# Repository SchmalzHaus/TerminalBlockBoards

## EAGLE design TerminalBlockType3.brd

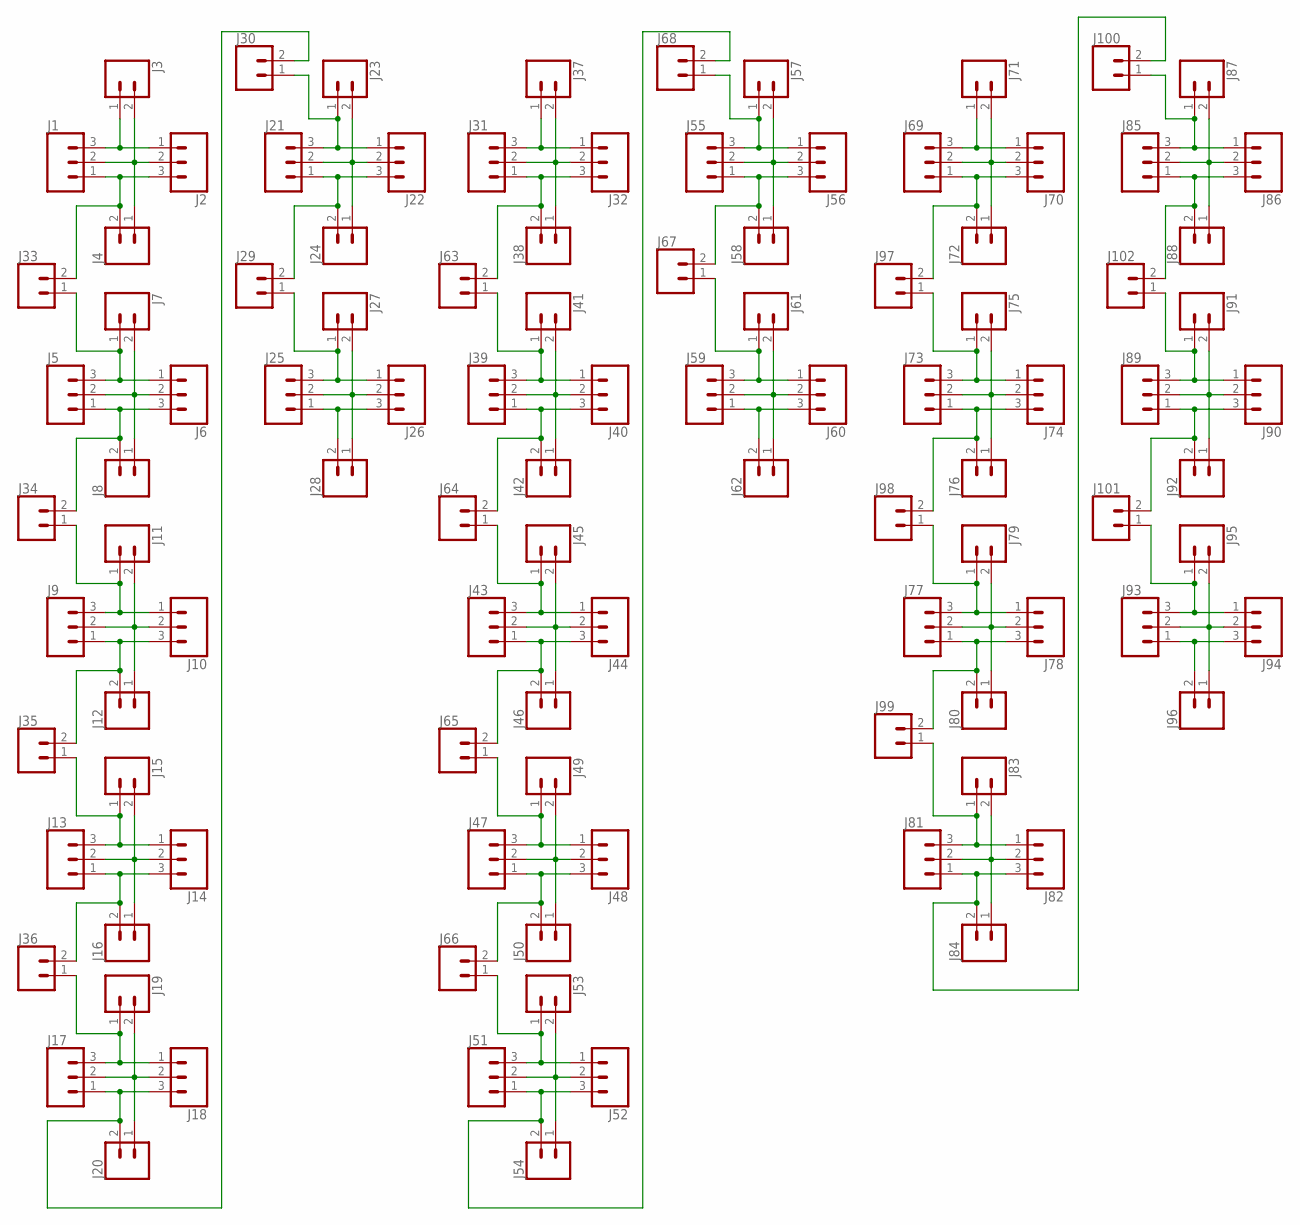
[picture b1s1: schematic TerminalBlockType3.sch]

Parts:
J1, J2, J5, J6, J9, J10, J13, J14, J17, J18, J21, J22, J25, J26, J31, J32, J39, J40, J43, J44, J47, J48, J51, J52, J55, J56, J59, J60, J69, J70, J73, J74, J77, J78, J81, J82, J85, J86, J89, J90, J93, J94: CONN_03SCREW_LOCK; SCREWTERMINAL-3.5MM-3_LOCK.007S
J3, J4, J7, J8, J11, J12, J15, J16, J19, J20, J23, J24, J27, J28, J29, J30, J33, J34, J35, J36, J37, J38, J41, J42, J45, J46, J49, J50, J53, J54, J57, J58, J61, J62, J63, J64, J65, J66, J67, J68, J71, J72, J75, J76, J79, J80, J83, J84, J87, J88, J91, J92, J95, J96, J97, J98, J99, J100, J101, J102: CONN_02; 1X02

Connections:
unnamed: J1.3, J2.1, J3.1
unnamed: J1.2, J2.2, J3.2, J4.1
unnamed: J1.1, J2.3, J4.2, J33.2
unnamed: J5.3, J6.1, J7.1, J33.1
unnamed: J5.2, J6.2, J7.2, J8.1
unnamed: J5.1, J6.3, J8.2, J34.2
unnamed: J9.3, J10.1, J11.1, J34.1
unnamed: J9.2, J10.2, J11.2, J12.1
unnamed: J9.1, J10.3, J12.2, J35.2
unnamed: J13.3, J14.1, J15.1, J35.1
unnamed: J13.2, J14.2, J15.2, J16.1
unnamed: J13.1, J14.3, J16.2, J36.2
unnamed: J17.3, J18.1, J19.1, J36.1
unnamed: J17.2, J18.2, J19.2, J20.1
unnamed: J17.1, J18.3, J20.2, J30.2
unnamed: J21.3, J22.1, J23.1, J30.1
unnamed: J21.2, J22.2, J23.2, J24.1
unnamed: J21.1, J22.3, J24.2, J29.2
unnamed: J25.3, J26.1, J27.1, J29.1
unnamed: J25.2, J26.2, J27.2, J28.1
unnamed: J25.1, J26.3, J28.2
unnamed: J31.3, J32.1, J37.1
unnamed: J31.2, J32.2, J37.2, J38.1
unnamed: J31.1, J32.3, J38.2, J63.2
unnamed: J39.3, J40.1, J41.1, J63.1
unnamed: J39.2, J40.2, J41.2, J42.1
unnamed: J39.1, J40.3, J42.2, J64.2
unnamed: J43.3, J44.1, J45.1, J64.1
unnamed: J43.2, J44.2, J45.2, J46.1
unnamed: J43.1, J44.3, J46.2, J65.2
unnamed: J47.3, J48.1, J49.1, J65.1
unnamed: J47.2, J48.2, J49.2, J50.1
unnamed: J47.1, J48.3, J50.2, J66.2
unnamed: J51.3, J52.1, J53.1, J66.1
unnamed: J51.2, J52.2, J53.2, J54.1
unnamed: J51.1, J52.3, J54.2, J68.2
unnamed: J55.3, J56.1, J57.1, J68.1
unnamed: J55.2, J56.2, J57.2, J58.1
unnamed: J55.1, J56.3, J58.2, J67.2
unnamed: J59.3, J60.1, J61.1, J67.1
unnamed: J59.2, J60.2, J61.2, J62.1
unnamed: J59.1, J60.3, J62.2
unnamed: J69.3, J70.1, J71.1
unnamed: J69.2, J70.2, J71.2, J72.1
unnamed: J69.1, J70.3, J72.2, J97.2
unnamed: J73.3, J74.1, J75.1, J97.1
unnamed: J73.2, J74.2, J75.2, J76.1
unnamed: J73.1, J74.3, J76.2, J98.2
unnamed: J77.3, J78.1, J79.1, J98.1
unnamed: J77.2, J78.2, J79.2, J80.1
unnamed: J77.1, J78.3, J80.2, J99.2
unnamed: J81.3, J82.1, J83.1, J99.1
unnamed: J81.2, J82.2, J83.2, J84.1
unnamed: J81.1, J82.3, J84.2, J100.2
unnamed: J85.3, J86.1, J87.1, J100.1
unnamed: J85.2, J86.2, J87.2, J88.1
unnamed: J85.1, J86.3, J88.2, J102.2
unnamed: J89.3, J90.1, J91.1, J102.1
unnamed: J89.2, J90.2, J91.2, J92.1
unnamed: J89.1, J90.3, J92.2, J101.2
unnamed: J93.3, J94.1, J95.1, J101.1
unnamed: J93.2, J94.2, J95.2, J96.1
unnamed: J93.1, J94.3, J96.2

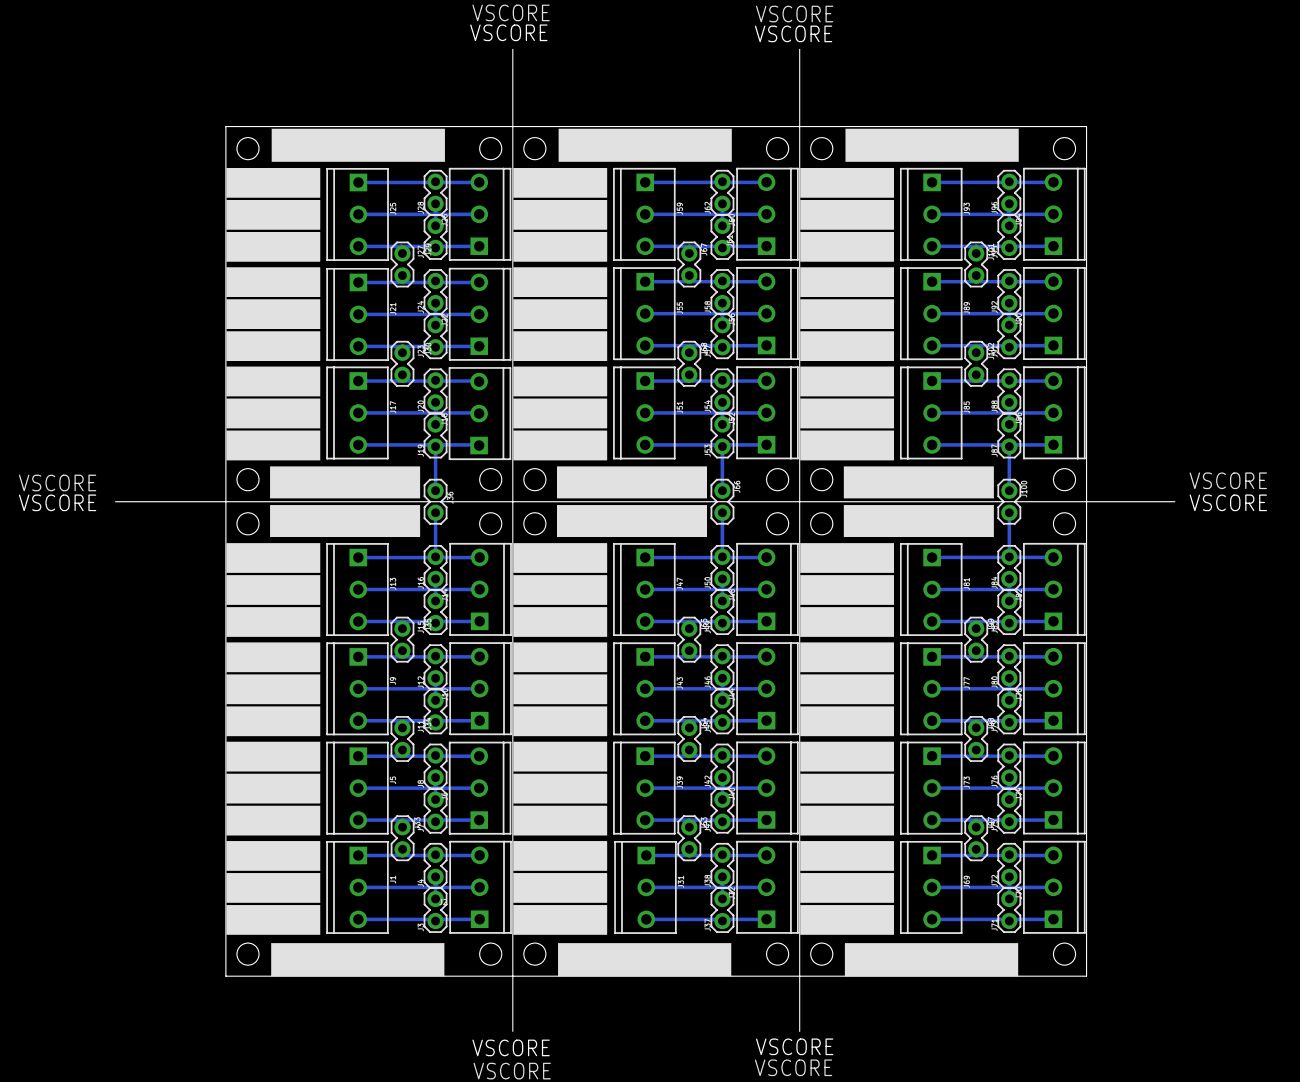
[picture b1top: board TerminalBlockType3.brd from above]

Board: 2 copper layers, 99.1 x 97.8 mm, 102 parts (0 on the bottom side), 63 nets.

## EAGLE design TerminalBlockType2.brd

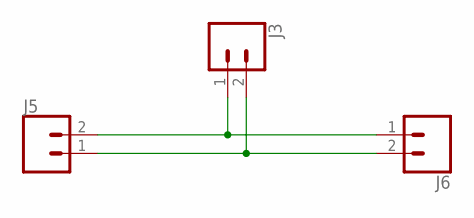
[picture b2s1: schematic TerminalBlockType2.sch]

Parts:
J3: CONN_02; 1X02
J5, J6: CONN_023.5MM_LOCK; SCREWTERMINAL-3.5MM-2_LOCK

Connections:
unnamed: J3.1, J5.2, J6.1
unnamed: J3.2, J5.1, J6.2

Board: 2 copper layers, 3 parts (0 on the bottom side), 2 nets, no tracks yet.

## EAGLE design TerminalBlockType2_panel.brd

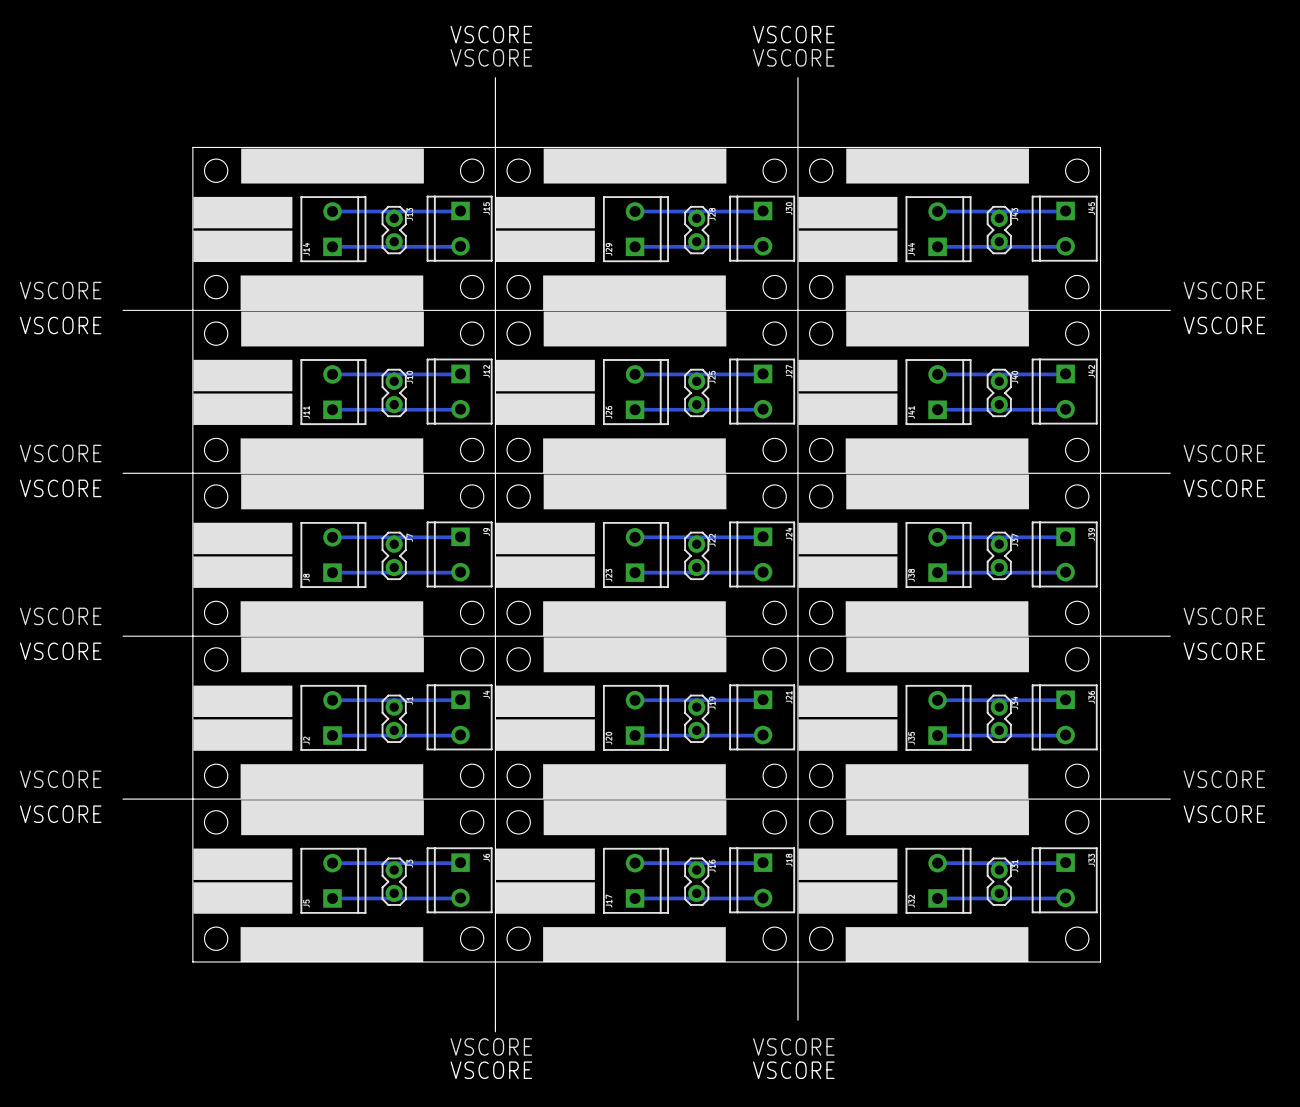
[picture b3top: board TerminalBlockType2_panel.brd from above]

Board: 2 copper layers, 114.3 x 104.1 mm, 45 parts (0 on the bottom side), 30 nets.

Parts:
J1, J3, J7, J10, J13, J16, J19, J22, J25, J28, J31, J34, J37, J40, J43: 1X02
J2, J4, J5, J6, J8, J9, J11, J12, J14, J15, J17, J18, J20, J21, J23, J24, J26, J27, J29, J30, J32, J33, J35, J36, J38, J39, J41, J42, J44, J45: SCREWTERMINAL-3.5MM-2_LOCK

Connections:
unnamed: J3.1, J5.2, J6.1
unnamed: J3.2, J5.1, J6.2
unnamed: J1.1, J2.2, J4.1
unnamed: J1.2, J2.1, J4.2
unnamed: J7.1, J8.2, J9.1
unnamed: J7.2, J8.1, J9.2
unnamed: J10.1, J11.2, J12.1
unnamed: J10.2, J11.1, J12.2
unnamed: J13.1, J14.2, J15.1
unnamed: J13.2, J14.1, J15.2
unnamed: J16.1, J17.2, J18.1
unnamed: J16.2, J17.1, J18.2
unnamed: J19.1, J20.2, J21.1
unnamed: J19.2, J20.1, J21.2
unnamed: J22.1, J23.2, J24.1
unnamed: J22.2, J23.1, J24.2
unnamed: J25.1, J26.2, J27.1
unnamed: J25.2, J26.1, J27.2
unnamed: J28.1, J29.2, J30.1
unnamed: J28.2, J29.1, J30.2
unnamed: J31.1, J32.2, J33.1
unnamed: J31.2, J32.1, J33.2
unnamed: J34.1, J35.2, J36.1
unnamed: J34.2, J35.1, J36.2
unnamed: J37.1, J38.2, J39.1
unnamed: J37.2, J38.1, J39.2
unnamed: J40.1, J41.2, J42.1
unnamed: J40.2, J41.1, J42.2
unnamed: J43.1, J44.2, J45.1
unnamed: J43.2, J44.1, J45.2

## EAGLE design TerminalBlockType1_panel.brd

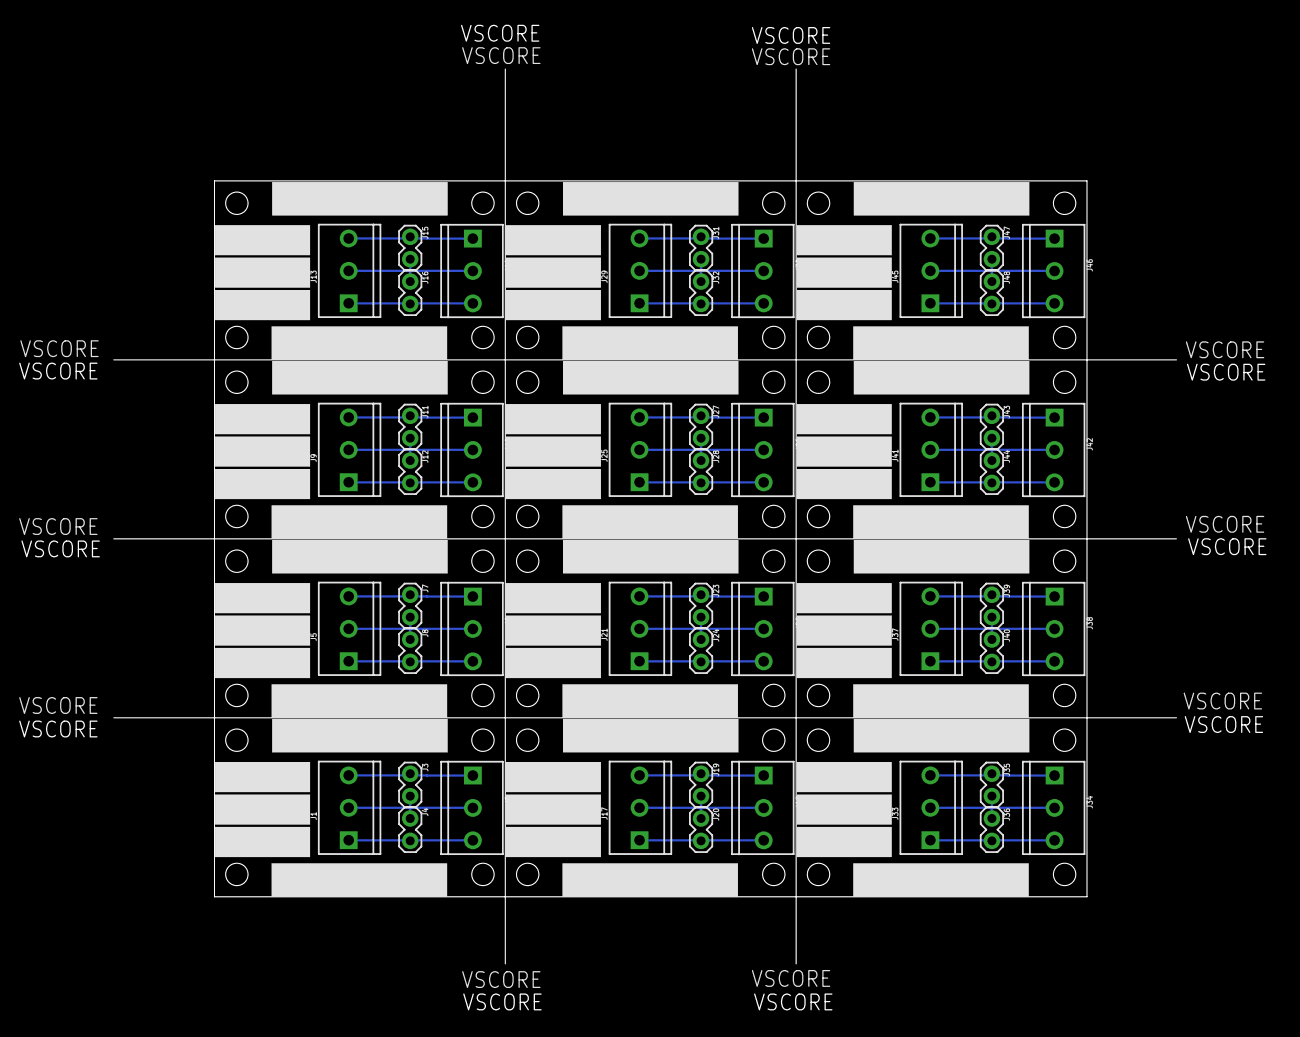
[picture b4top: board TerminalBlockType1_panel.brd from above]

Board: 2 copper layers, 120.7 x 101.6 mm, 48 parts (0 on the bottom side), 36 nets.

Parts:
J1, J2, J5, J6, J9, J10, J13, J14, J17, J18, J21, J22, J25, J26, J29, J30, J33, J34, J37, J38, J41, J42, J45, J46: SCREWTERMINAL-3.5MM-3_LOCK.007S
J3, J4, J7, J8, J11, J12, J15, J16, J19, J20, J23, J24, J27, J28, J31, J32, J35, J36, J39, J40, J43, J44, J47, J48: 1X02

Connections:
unnamed: J1.3, J2.1, J3.1
unnamed: J1.2, J2.2, J3.2, J4.1
unnamed: J1.1, J2.3, J4.2
unnamed: J5.3, J6.1, J7.1
unnamed: J5.2, J6.2, J7.2, J8.1
unnamed: J5.1, J6.3, J8.2
unnamed: J9.3, J10.1, J11.1
unnamed: J9.2, J10.2, J11.2, J12.1
unnamed: J9.1, J10.3, J12.2
unnamed: J13.3, J14.1, J15.1
unnamed: J13.2, J14.2, J15.2, J16.1
unnamed: J13.1, J14.3, J16.2
unnamed: J17.3, J18.1, J19.1
unnamed: J17.2, J18.2, J19.2, J20.1
unnamed: J17.1, J18.3, J20.2
unnamed: J21.3, J22.1, J23.1
unnamed: J21.2, J22.2, J23.2, J24.1
unnamed: J21.1, J22.3, J24.2
unnamed: J25.3, J26.1, J27.1
unnamed: J25.2, J26.2, J27.2, J28.1
unnamed: J25.1, J26.3, J28.2
unnamed: J29.3, J30.1, J31.1
unnamed: J29.2, J30.2, J31.2, J32.1
unnamed: J29.1, J30.3, J32.2
unnamed: J33.3, J34.1, J35.1
unnamed: J33.2, J34.2, J35.2, J36.1
unnamed: J33.1, J34.3, J36.2
unnamed: J37.3, J38.1, J39.1
unnamed: J37.2, J38.2, J39.2, J40.1
unnamed: J37.1, J38.3, J40.2
unnamed: J41.3, J42.1, J43.1
unnamed: J41.2, J42.2, J43.2, J44.1
unnamed: J41.1, J42.3, J44.2
unnamed: J45.3, J46.1, J47.1
unnamed: J45.2, J46.2, J47.2, J48.1
unnamed: J45.1, J46.3, J48.2

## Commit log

2019-04-19 First commit - nothing much there yet.
2019-04-19 Type 2 beginning.
2019-04-20 Finished Type 3 and type 1.
2019-04-20 All three boards done and sent to JLC for fab.
2019-04-20 Updated screw hole size to match better with #2 wood screws. Resubmitted to JLC.

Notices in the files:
parts and their libraries:
SparkFun-Connectors: Licensing: Creative Commons ShareAlike 4.0 International - https://creativecommons.org/licenses/by-sa/4.0
